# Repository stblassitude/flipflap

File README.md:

# Controller for OMEGA OM3021 Split-Flap Displays

# Overview
The controller board uses an D1 mini ESP8266 microcontroller to control a number of outputs going to the displays, and read inputs connected to the display encodes, which give the current position of the rotor with the split flaps.

The controller can address 8 lines and 15 columns, for a total of 120 characters. With the displays currently available to us, we're using 6 lines with 11 columns, for a total of 66 characters.

The schematic [flipflap-sch.pdf](flipflap-sch.pdf) and the assembly diagram [flipflap-pcb.pdf](flipflap-pcb.pdf) show the details of the board.

# Software
An Arduino sketch can be found in [arduino/flipflap](arduino/flipflap).

# Documentation OMEGA OM3021
Documentation for the split-flap display model can be found in [docs/](docs/). [Theory of Operation](docs/theory-of-operation.md) tries to explain how a microcontroller can control the displays.

# Arduino Setup

* https://arduino.github.io/arduino-cli/0.29/getting-started/
* https://medium.com/@thomas.kilmar/arduino-cli-with-visual-studio-code-on-macos-d2ad32ff0276

# Further Reading

We're not the only ones working with these modules.

* [Tim's SplitFlap Clock - Part I (Electronics)](https://web.archive.org/web/20220701175858/https://www.way2.net/2022/03/14/splitflap/). Unfortunately, the software part seems to never have been published.

# Version History

## 1.0

### Known Issues

* /ADC4 to /ADC7 are swapped when looking at the register outputs. This can easily be adjusted in the ADC cable.

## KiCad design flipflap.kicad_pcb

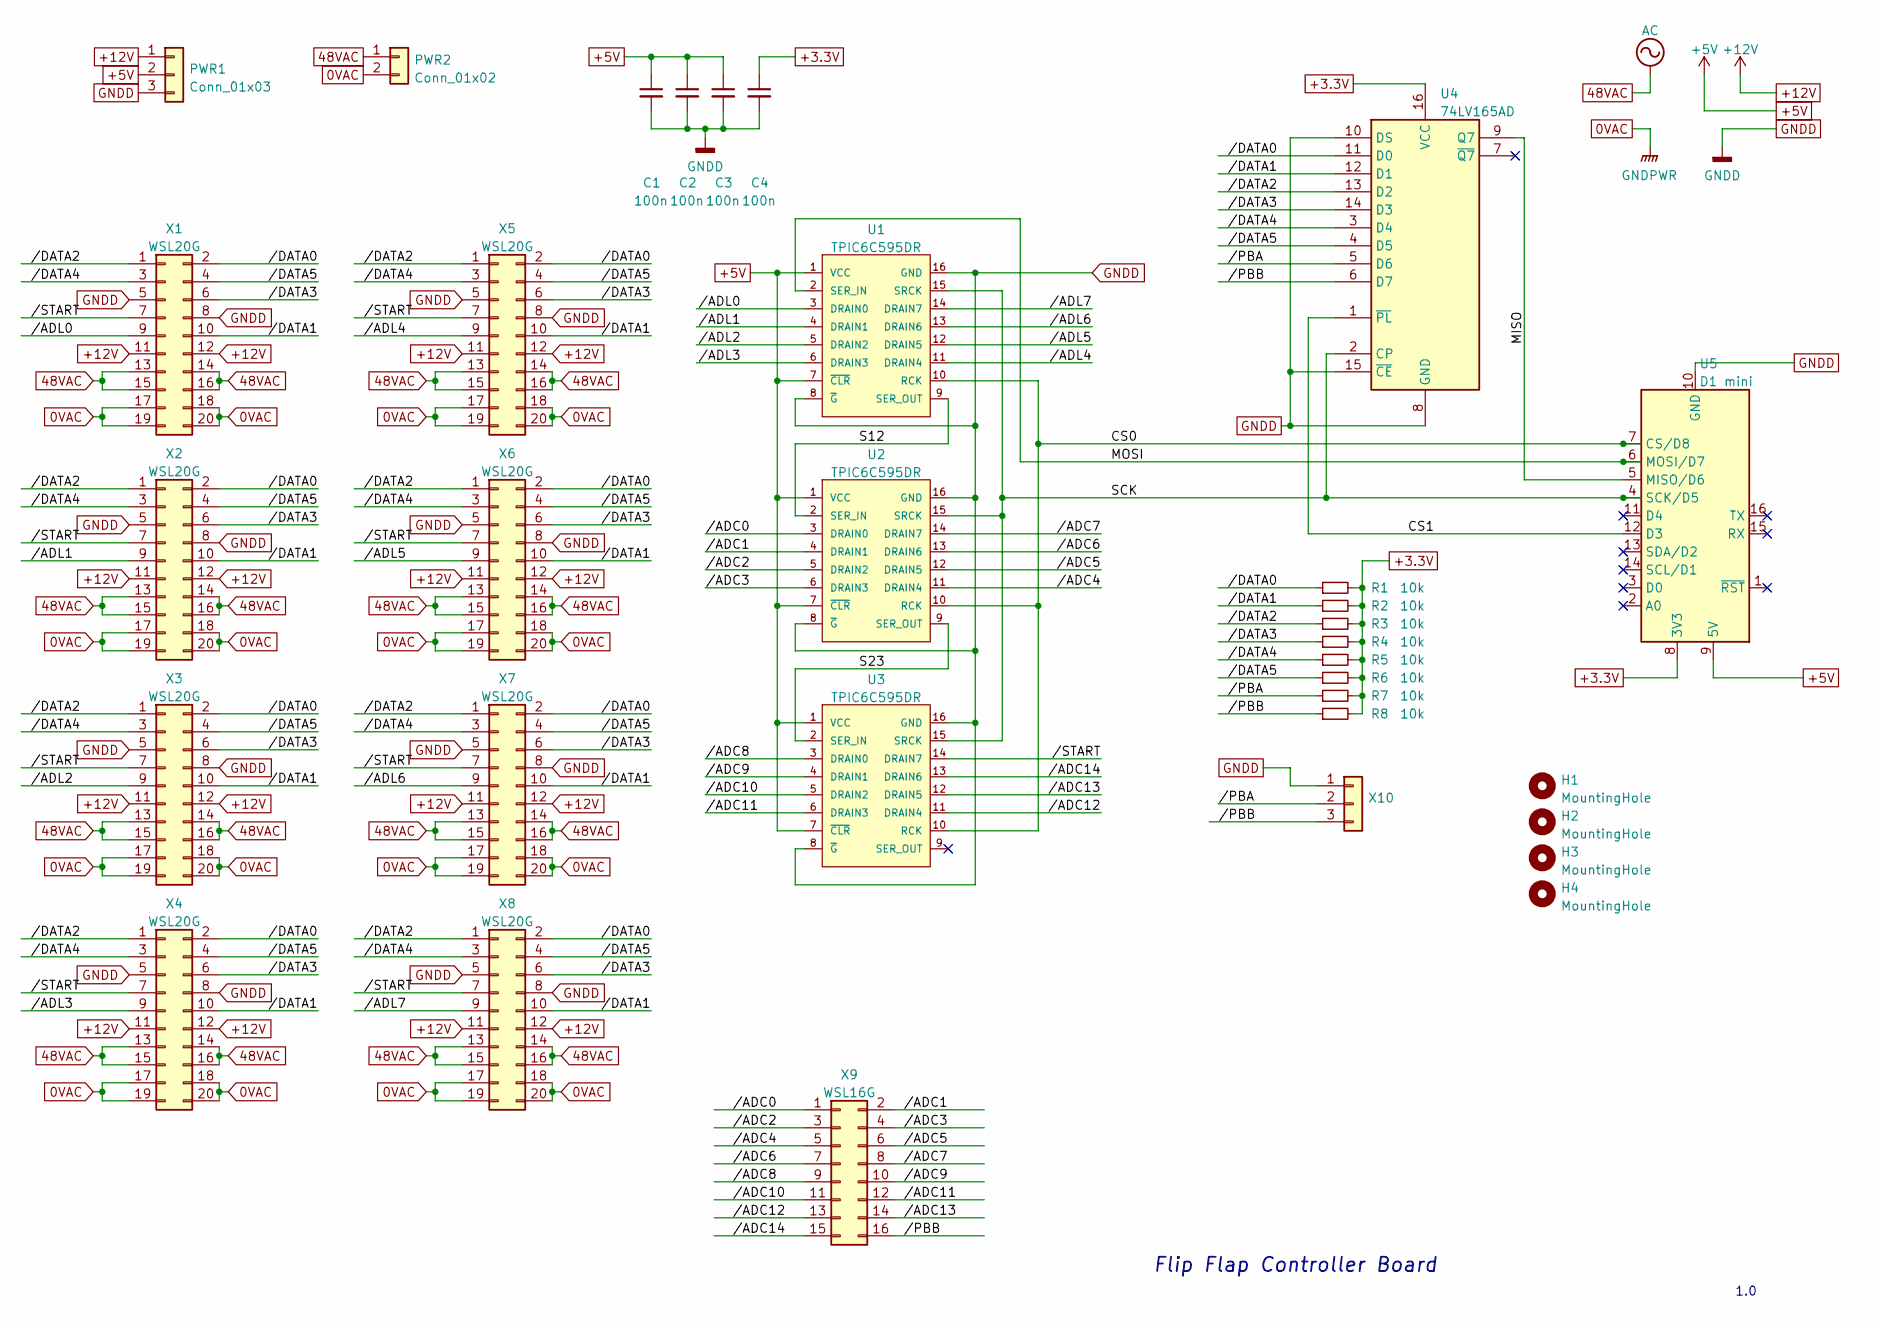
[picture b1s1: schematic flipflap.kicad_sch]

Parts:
C1, C2, C4: 100n; C_0603_1608Metric; JLCPCB C14663
C3: 100n; C_0603_1608Metric
H1, H2, H3, H4: MountingHole; MountingHole_3.5mm
PWR1: Conn_01x03; PinHeader_1x03_P2.54mm_Vertical
PWR2: Conn_01x02; PinHeader_1x02_P2.54mm_Vertical
R1, R2, R3, R4, R5, R6, R7, R8: 10k; R_0603_1608Metric; JLCPCB C4184
U1, U2, U3: TPIC6C595DR; SOIC-16_3.9x9.9mm_P1.27mm; JLCPCB C350572
U4: 74LV165AD; SOIC-16_3.9x9.9mm_P1.27mm; JLCPCB C478150
U5: D1 mini; WEMOS_D1_mini_light
X1, X2, X3, X4, X5, X6, X7, X8: WSL20G; IDC-Header_2x10_P2.54mm_Vertical
X9: WSL16G; IDC-Header_2x08_P2.54mm_Vertical
X10: Conn_01x03; PinHeader_1x03_P2.54mm_Vertical

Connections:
0VAC: PWR2.2, X1.17, X1.18, X1.19, X1.20, X2.17, X2.18, X2.19, X2.20, X3.17, X3.18, X3.19, X3.20, X4.17, X4.18, X4.19, X4.20, X5.17, X5.18, X5.19, X5.20, X6.17, X6.18, X6.19, X6.20, X7.17, X7.18, X7.19, X7.20, X8.17, X8.18, X8.19, X8.20
48VAC: PWR2.1, X1.13, X1.14, X1.15, X1.16, X2.13, X2.14, X2.15, X2.16, X3.13, X3.14, X3.15, X3.16, X4.13, X4.14, X4.15, X4.16, X5.13, X5.14, X5.15, X5.16, X6.13, X6.14, X6.15, X6.16, X7.13, X7.14, X7.15, X7.16, X8.13, X8.14, X8.15, X8.16
+3.3V: C4.1, R1.2, R2.2, R3.2, R4.2, R5.2, R6.2, R7.2, R8.2, U4.16 (VCC), U5.8 (3V3)
+5V: C1.1, C2.1, C3.1, PWR1.2, U1.1 (VCC), U1.7 (~CLR), U2.1 (VCC), U2.7 (~CLR), U3.1 (VCC), U3.7 (~CLR), U5.9 (5V)
+12V: PWR1.1, X1.11, X1.12, X2.11, X2.12, X3.11, X3.12, X4.11, X4.12, X5.11, X5.12, X6.11, X6.12, X7.11, X7.12, X8.11, X8.12
/CS0: U1.10 (RCK), U2.10 (RCK), U3.10 (RCK), U5.7 (CS/D8)
/CS1: U4.1 (~PL), U5.12 (D3)
/MISO: U4.9 (Q7), U5.5 (MISO/D6)
/MOSI: U1.2 (SER_IN), U5.6 (MOSI/D7)
/S12: U1.9 (SER_OUT), U2.2 (SER_IN)
/S23: U2.9 (SER_OUT), U3.2 (SER_IN)
/SCK: U1.15 (SRCK), U2.15 (SRCK), U3.15 (SRCK), U4.2 (CP), U5.4 (SCK/D5)
//ADC0: U2.3 (DRAIN0), X9.1
//ADC1: U2.4 (DRAIN1), X9.2
//ADC2: U2.5 (DRAIN2), X9.3
//ADC3: U2.6 (DRAIN3), X9.4
//ADC4: U2.11 (DRAIN4), X9.5
//ADC5: U2.12 (DRAIN5), X9.6
//ADC6: U2.13 (DRAIN6), X9.7
//ADC7: U2.14 (DRAIN7), X9.8
//ADC8: U3.3 (DRAIN0), X9.9
//ADC9: U3.4 (DRAIN1), X9.10
//ADC10: U3.5 (DRAIN2), X9.11
//ADC11: U3.6 (DRAIN3), X9.12
//ADC12: U3.11 (DRAIN4), X9.13
//ADC13: U3.12 (DRAIN5), X9.14
//ADC14: U3.13 (DRAIN6), X9.15
//ADL0: U1.3 (DRAIN0), X1.9
//ADL1: U1.4 (DRAIN1), X2.9
//ADL2: U1.5 (DRAIN2), X3.9
//ADL3: U1.6 (DRAIN3), X4.9
//ADL4: U1.11 (DRAIN4), X5.9
//ADL5: U1.12 (DRAIN5), X6.9
//ADL6: U1.13 (DRAIN6), X7.9
//ADL7: U1.14 (DRAIN7), X8.9
//DATA0: R1.1, U4.11 (D0), X1.2, X2.2, X3.2, X4.2, X5.2, X6.2, X7.2, X8.2
//DATA1: R2.1, U4.12 (D1), X1.10, X2.10, X3.10, X4.10, X5.10, X6.10, X7.10, X8.10
//DATA2: R3.1, U4.13 (D2), X1.1, X2.1, X3.1, X4.1, X5.1, X6.1, X7.1, X8.1
//DATA3: R4.1, U4.14 (D3), X1.6, X2.6, X3.6, X4.6, X5.6, X6.6, X7.6, X8.6
//DATA4: R5.1, U4.3 (D4), X1.3, X2.3, X3.3, X4.3, X5.3, X6.3, X7.3, X8.3
//DATA5: R6.1, U4.4 (D5), X1.4, X2.4, X3.4, X4.4, X5.4, X6.4, X7.4, X8.4
//PBA: R7.1, U4.5 (D6), X10.2
//PBB: R8.1, U4.6 (D7), X9.16, X10.3
//START: U3.14 (DRAIN7), X1.7, X2.7, X3.7, X4.7, X5.7, X6.7, X7.7, X8.7
GNDD: C1.2, C2.2, C3.2, C4.2, PWR1.3, U1.8 (~G), U1.16 (GND), U2.8 (~G), U2.16 (GND), U3.8 (~G), U3.16 (GND), U4.8 (GND), U4.10 (DS), U4.15 (~CE), U5.10 (GND), X1.5, X1.8, X2.5, X2.8, X3.5, X3.8, X4.5, X4.8, X5.5, X5.8, X6.5, X6.8, X7.5, X7.8, X8.5, X8.8, X10.1

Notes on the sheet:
Flip Flap Controller Board
1.0

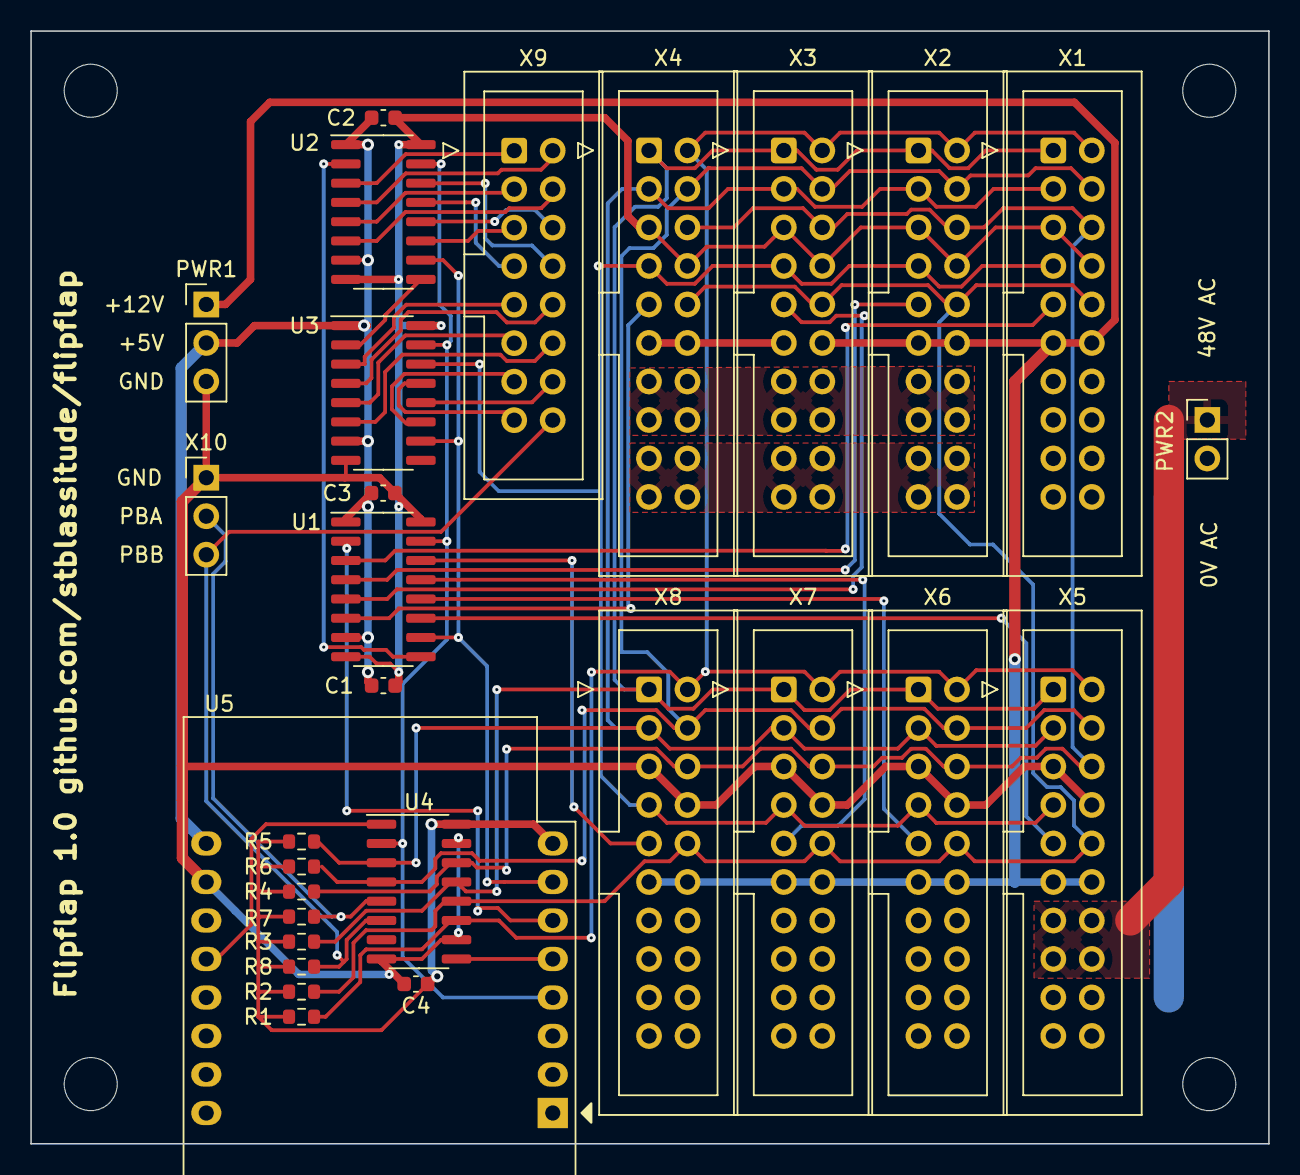
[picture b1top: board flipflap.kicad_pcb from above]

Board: 2 copper layers, 81.7 x 73.4 mm, 33 parts (0 on the bottom side), 45 nets.

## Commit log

2023-02-06 First draft of the schematics for the new controller board
2023-02-06 Properly exclude autosaved files
2023-02-06 Add footprints to all parts
2023-02-07 Completed PCB, populated on both sides.
2023-02-08 Complete PCB with components only on one side, some corrections included
2023-02-09 As ordered from JLCPCB
2023-02-09 Add some documentation
2023-02-09 Link more docs
2023-02-09 Add Apache 2.0 license
2023-02-09 Fix ADC4 to ADC7 (were swapped)
2023-02-25 Controller first draft
2023-02-25 Working with two displays
2023-02-25 Optimize timing
2023-02-26 Add web server
2023-02-26 Small optimizations
2023-02-27 First draft of an Arduino sketch to control the displays.
